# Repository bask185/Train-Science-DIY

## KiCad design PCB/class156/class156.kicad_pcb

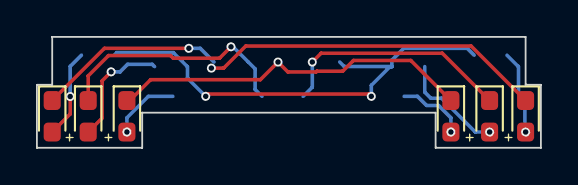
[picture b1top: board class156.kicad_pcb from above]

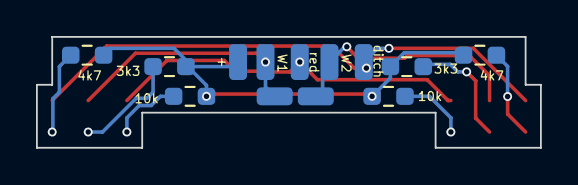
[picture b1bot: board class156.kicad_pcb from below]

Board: 2 copper layers, 28.0 x 6.2 mm, 19 parts (13 on the bottom side), 11 nets.

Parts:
D1, D2, D3, D4, D5, D6: LED; LED_0603_1608Metric_Pad1.05x0.95mm_HandSolder
J1: ditch; SolderWirePad_1x01_SMD_1x2mm
J2, J6: W1; SolderWirePad_1x01_SMD_1x2mm
J3: red; SolderWirePad_1x01_SMD_1x2mm
J4: Conn_01x01_Pin; SolderWirePad_1x01_SMD_1x2mm
J5, J7: W3; SolderWirePad_1x01_SMD_1x2mm
R1, R6: 4k7; R_0603_smalltext
R2, R5: 3k3; R_0603_smalltext
R3, R4: 10k; R_0603_smalltext

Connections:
unnamed: D1.2 (A), R1.2
unnamed: D1.1 (K), D6.1 (K), J1.1
unnamed: D2.2 (A), R2.2
unnamed: D2.1 (K), J2.1, J6.1
unnamed: D3.2 (A), R3.2
unnamed: D3.1 (K), D4.1 (K), J3.1
unnamed: D4.2 (A), R4.2
unnamed: D5.2 (A), R5.2
unnamed: D5.1 (K), J5.1, J7.1
unnamed: D6.2 (A), R6.2
VCC: J4.1, R1.1, R2.1, R3.1, R4.1, R5.1, R6.1

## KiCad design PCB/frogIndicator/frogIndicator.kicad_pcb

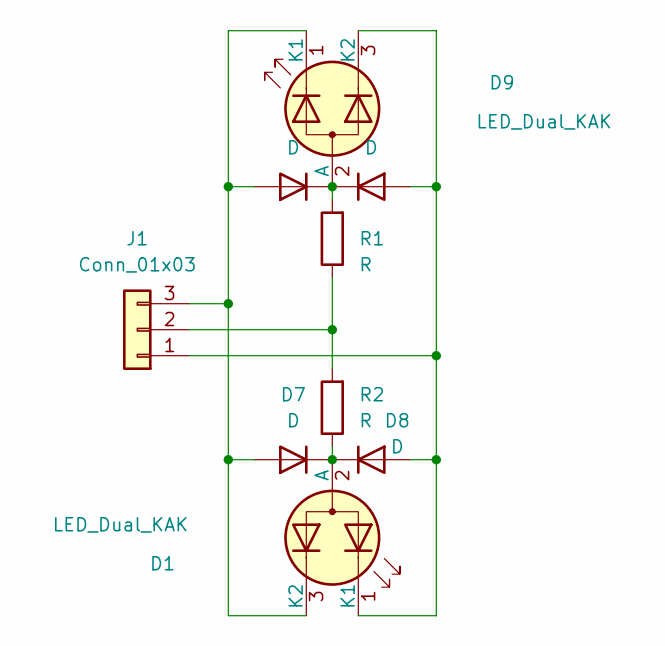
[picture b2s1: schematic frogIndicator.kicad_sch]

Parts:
D1, D9: LED_Dual_KAK; LED_D3.0mm-3
D5, D6, D7, D8: D; D_DO-34_SOD68_P7.62mm_Horizontal
J1: Conn_01x03; TerminalBlock_Phoenix_MKDS-1,5-3-5.08_1x03_P5.08mm_Horizont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
R1, R2: R; R_Axial_DIN0204_L3.6mm_D1.6mm_P7.62mm_Horizontal

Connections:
unnamed: D1.2 (A), D7.1 (K), D8.1 (K), R2.1
unnamed: D1.1 (K1), D6.2 (A), D8.2 (A), D9.3 (K2), J1.1
unnamed: D1.3 (K2), D5.2 (A), D7.2 (A), D9.1 (K1), J1.3
unnamed: D5.1 (K), D6.1 (K), D9.2 (A), R1.2
unnamed: J1.2, R1.1, R2.2

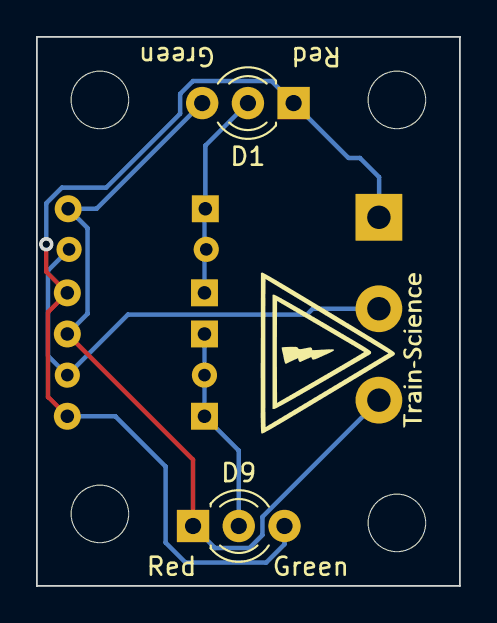
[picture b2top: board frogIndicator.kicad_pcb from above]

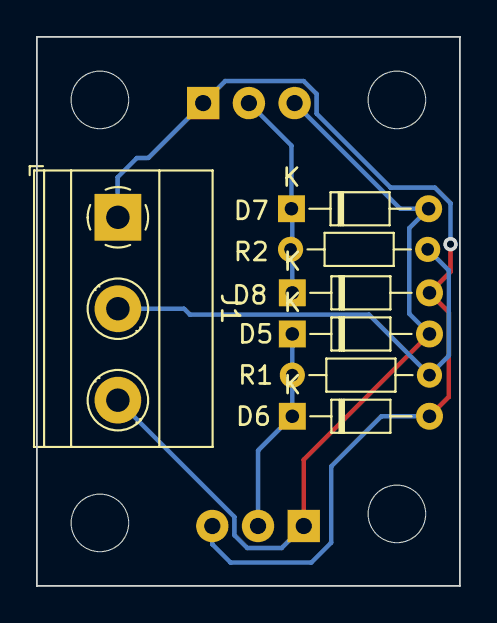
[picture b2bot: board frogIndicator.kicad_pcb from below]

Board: 2 copper layers, 23.5 x 30.5 mm, 9 parts (7 on the bottom side), 5 nets.

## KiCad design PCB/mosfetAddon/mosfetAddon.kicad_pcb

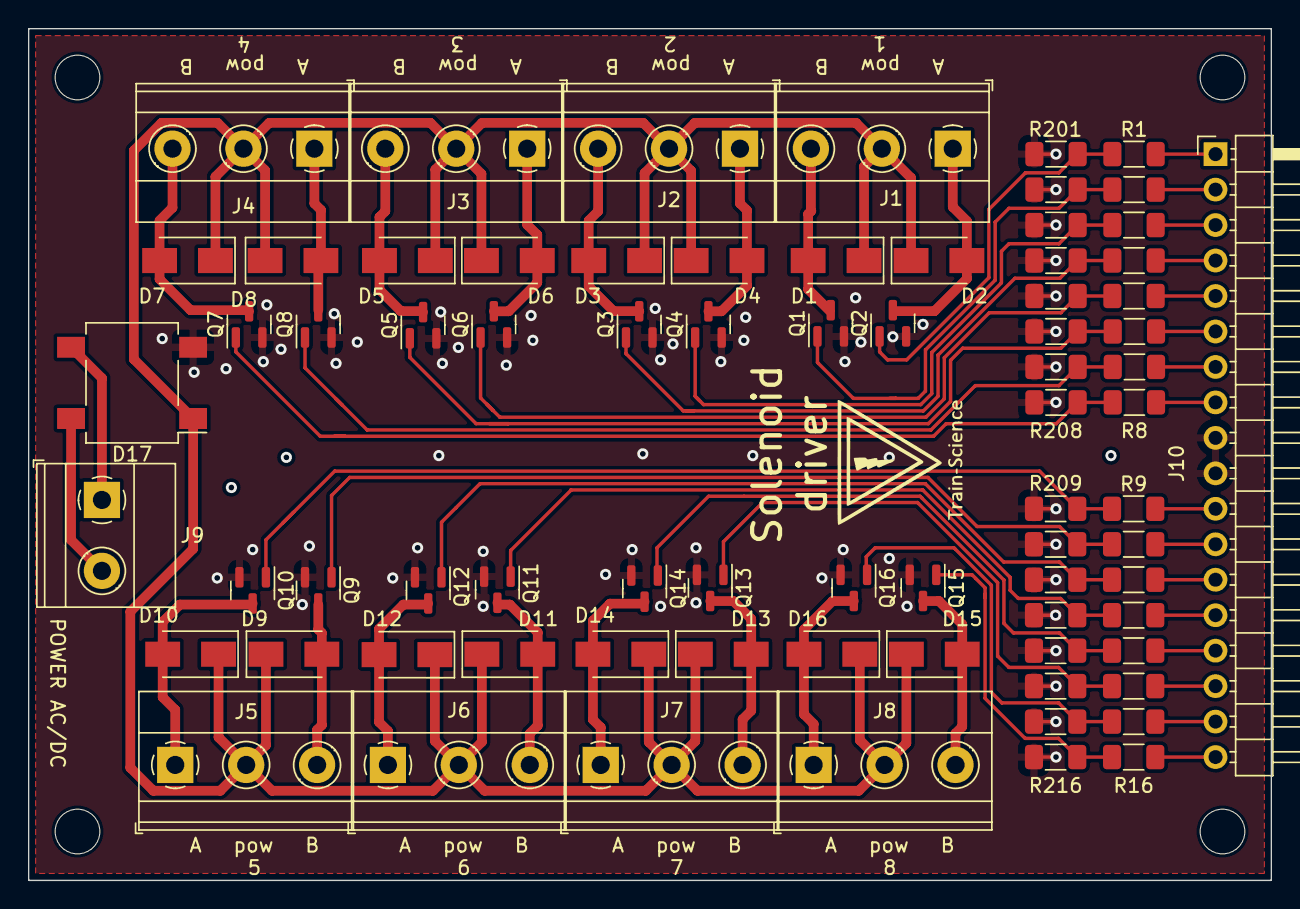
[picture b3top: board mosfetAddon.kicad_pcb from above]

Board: 2 copper layers, 89.0 x 61.0 mm, 75 parts (0 on the bottom side), 52 nets.

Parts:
D1, D2, D3, D4, D5, D6, D7, D8, D9, D10, D11, D12, D13, D14, D15, D16: D; D_SMA
D17: D_Bridge_+-AA; Diode_Bridge_Diotec_SO-DIL-Slim
J1, J2, J3, J4, J5, J6, J7, J8: coil; TerminalBlock_Phoenix_MKDS-1,5-3-5.08_1x03_P5.08mm_Horizont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
J9: pow; TerminalBlock_Phoenix_MKDS-1,5-2-5.08_1x02_P5.08mm_Horizont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
J10: Conn_01x18_Male; PinHeader_1x18_P2.54mm_Horizontal
Q1, Q2, Q3, Q4, Q5, Q6, Q7, Q8, Q9, Q10, Q11, Q12, Q13, Q14, Q15, Q16: AO3400A; SOT-23
R1, R2, R3, R4, R5, R6, R7, R8, R9, R10, R11, R12, R13, R14, R15, R16: 22R; R_1206_3216Metric_Pad1.30x1.75mm_HandSolder
R201, R202, R203, R204, R205, R206, R207, R208, R209, R210, R211, R212, R213, R214, R215, R216: 10k; R_1206_3216Metric_Pad1.30x1.75mm_HandSolder

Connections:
GND: D17.2 (-), J10.9, J10.10, Q1.2 (S), Q2.2 (S), Q3.2 (S), Q4.2 (S), Q5.2 (S), Q6.2 (S), Q7.2 (S), Q8.2 (S), Q9.2 (S), Q10.2 (S), Q11.2 (S), Q12.2 (S), Q13.2 (S), Q14.2 (S), Q15.2 (S), Q16.2 (S), R201.1, R202.1, R203.1, R204.1, R205.1, R206.1, R207.1, R208.1, R209.1, R210.1, R211.1, R212.1, R213.1, R214.1, R215.1, R216.1
unnamed: D17.3, J9.1
unnamed: D17.4, J9.2
unnamed: Q2.1 (G), R1.2, R201.2
unnamed: Q1.1 (G), R2.2, R202.2
unnamed: Q4.1 (G), R3.2, R203.2
unnamed: Q3.1 (G), R4.2, R204.2
unnamed: Q6.1 (G), R5.2, R205.2
unnamed: Q5.1 (G), R6.2, R206.2
unnamed: Q8.1 (G), R7.2, R207.2
unnamed: Q7.1 (G), R8.2, R208.2
unnamed: Q10.1 (G), R9.2, R209.2
unnamed: Q9.1 (G), R10.2, R210.2
unnamed: Q12.1 (G), R11.2, R211.2
unnamed: Q11.1 (G), R12.2, R212.2
unnamed: Q14.1 (G), R13.2, R213.2
unnamed: Q13.1 (G), R14.2, R214.2
unnamed: Q16.1 (G), R15.2, R215.2
unnamed: Q15.1 (G), R16.2, R216.2
coil1L: D1.2 (A), J1.3, Q1.3 (D)
coil1R: D2.2 (A), J1.1, Q2.3 (D)
coil2L: D3.2 (A), J2.3, Q3.3 (D)
coil2R: D4.2 (A), J2.1, Q4.3 (D)
coil3L: D5.2 (A), J3.3, Q5.3 (D)
coil3R: D6.2 (A), J3.1, Q6.3 (D)
coil4L: D7.2 (A), J4.3, Q7.3 (D)
coil4R: D8.2 (A), J4.1, Q8.3 (D)
coil5L: D9.2 (A), J5.3, Q9.3 (D)
coil5R: D10.2 (A), J5.1, Q10.3 (D)
coil6L: D11.2 (A), J6.3, Q11.3 (D)
coil6R: D12.2 (A), J6.1, Q12.3 (D)
coil7L: D13.2 (A), J7.3, Q13.3 (D)
coil7R: D14.2 (A), J7.1, Q14.3 (D)
coil8L: D15.2 (A), J8.3, Q15.3 (D)
coil8R: D16.2 (A), J8.1, Q16.3 (D)
gate1L: J10.2, R2.1
gate1R: J10.1, R1.1
gate2L: J10.4, R4.1
gate2R: J10.3, R3.1
gate3L: J10.6, R6.1
gate3R: J10.5, R5.1
gate4L: J10.8, R8.1
gate4R: J10.7, R7.1
gate5L: J10.12, R10.1
gate5R: J10.11, R9.1
gate6L: J10.14, R12.1
gate6R: J10.13, R11.1
gate7L: J10.16, R14.1
gate7R: J10.15, R13.1
gate8L: J10.18, R16.1
gate8R: J10.17, R15.1
pow: D1.1 (K), D2.1 (K), D3.1 (K), D4.1 (K), D5.1 (K), D6.1 (K), D7.1 (K), D8.1 (K), D9.1 (K), D10.1 (K), D11.1 (K), D12.1 (K), D13.1 (K), D14.1 (K), D15.1 (K), D16.1 (K), D17.1 (+), J1.2, J2.2, J3.2, J4.2, J5.2, J6.2, J7.2, J8.2

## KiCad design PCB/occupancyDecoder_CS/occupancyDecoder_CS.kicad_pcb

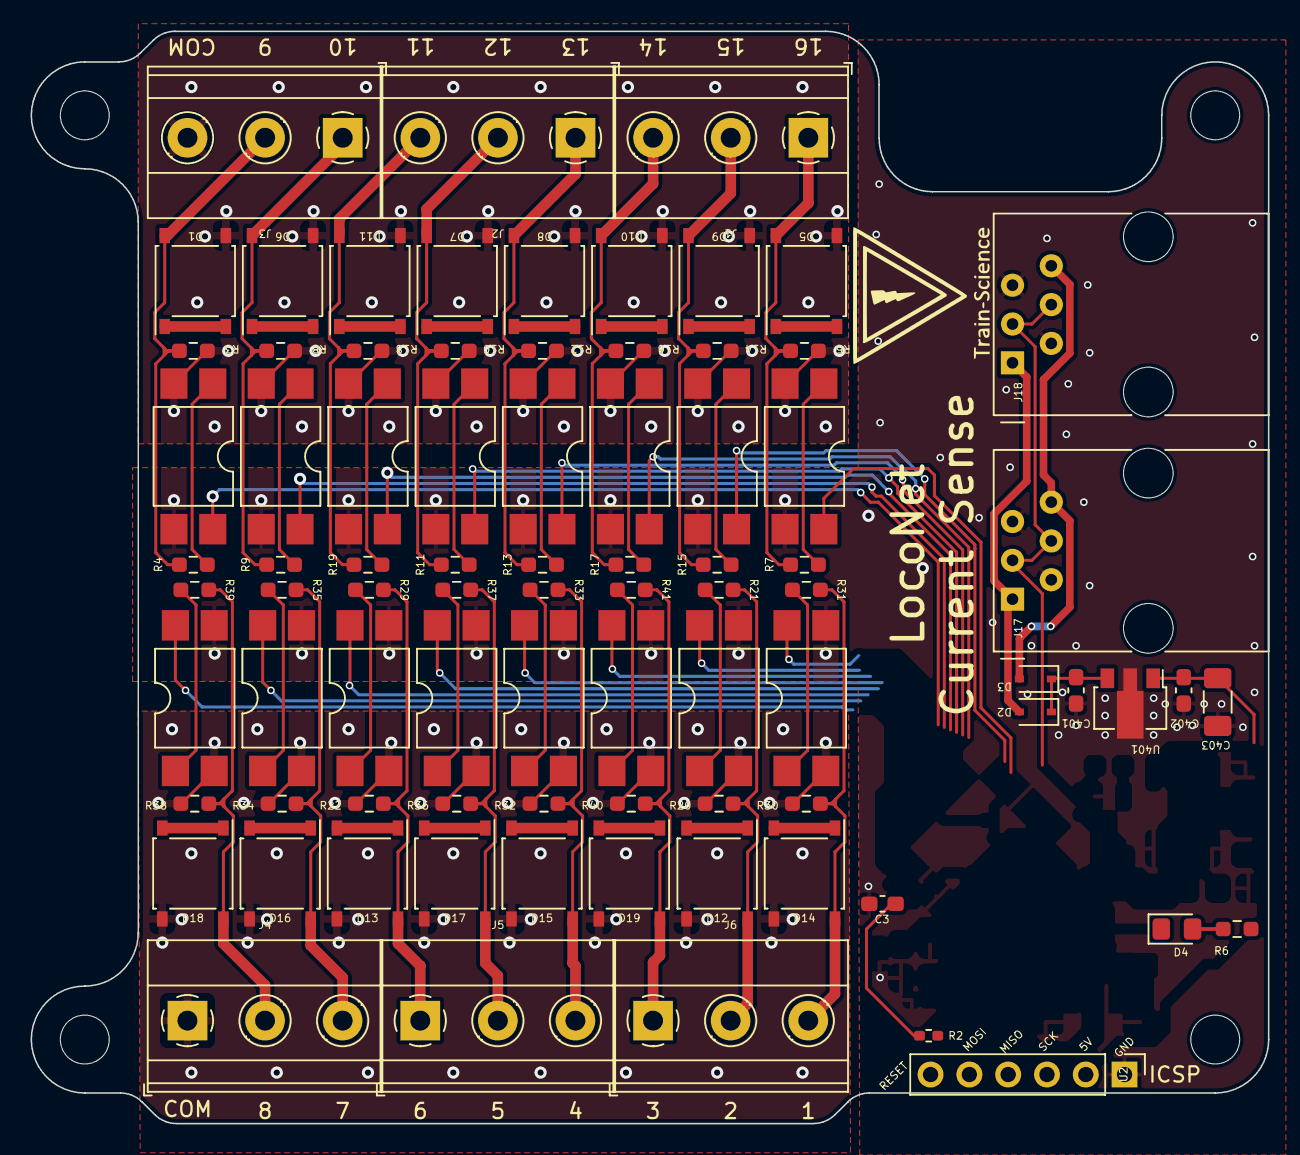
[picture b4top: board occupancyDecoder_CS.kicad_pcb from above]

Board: 2 copper layers, 81.0 x 71.5 mm, 83 parts (0 on the bottom side), 61 nets.

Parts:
C3, C402: 100nF; C_0603_1608Metric_Pad1.08x0.95mm_HandSolder
C401: 330nF; C_0603_1608Metric_Pad1.08x0.95mm_HandSolder
C403: 100uF; C_1206_3216Metric_Pad1.33x1.80mm_HandSolder
D1, D5, D6, D7, D8, D9, D10, D11, D12, D13, D14, D15, D16, D17, D18, D19: ABS2; Diode_Bridge_Diotec_ABS
D2, D3: D; D_SOD-323
D4: LED; LED_0805_2012Metric_Pad1.15x1.40mm_HandSolder
J1, J2, J3, J4, J5, J6: Screw_Terminal_01x03; TerminalBlock_Phoenix_MKDS-1,5-3-5.08_1x03_P5.08mm_Horizont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
J17, J18: RJ12; RJ12_Amphenol_54601
R2: 10k; R_0402_1005Metric_Pad0.72x0.64mm_HandSolder
R3, R5, R8, R10, R12, R14, R16, R18, R20, R22, R30, R32, R34, R36, R38, R40: 4k7; R_0603_smalltext
R4, R7, R9, R11, R13, R15, R17, R19, R21, R29, R31, R33, R35, R37, R39, R41: 47R; R_0603_smalltext
R6: 6k2; R_0603_1608Metric_Pad0.98x0.95mm_HandSolder
U2: ICSP; PinHeader_1x06_P2.54mm_Vertical
U3, U4, U5, U6, U7, U8, U9, U10, U11, U12, U13, U14, U16, U17, U18, U19: EL814; SMDIP-4_W9.53mm
U401: L78L05_SOT89; SOT-89-3

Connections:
+5V: C3.2, C402.1, C403.1, R2.1, R6.1, U2.2, U401.1 (OUT)
/GPIO_A/CS1/COM: D12.3, D13.3, D14.3, D15.3, D16.3, D17.3, D18.3, D19.3, J4.1, R20.2, R22.2, R30.2, R32.2, R34.2, R36.2, R38.2, R40.2, U11.2, U12.2, U13.2, U14.2, U16.2, U17.2, U18.2, U19.2
/GPIO_A/CS1/Track: D14.4, J6.3, R30.1, R31.1
/GPIO_A/CS2/Track: D12.4, J6.2, R20.1, R21.1
/GPIO_A/CS3/Track: D19.4, J6.1, R40.1, R41.1
/GPIO_A/CS4/Track: D15.4, J5.3, R32.1, R33.1
/GPIO_A/CS5/Track: D17.4, J5.2, R36.1, R37.1
/GPIO_A/CS6/Track: D13.4, J5.1, R22.1, R29.1
/GPIO_A/CS7/Track: D16.4, J4.3, R34.1, R35.1
/GPIO_A/CS8/Track: D18.4, J4.2, R38.1, R39.1
/GPIO_A/GPIO_A5: U2.5, U17.4
/GPIO_A/GPIO_A6: U2.4, U12.4
/GPIO_B/CS1/COM: D1.3, D5.3, D6.3, D7.3, D8.3, D9.3, D10.3, D11.3, J3.3, R3.2, R5.2, R8.2, R10.2, R12.2, R14.2, R16.2, R18.2, U3.2, U4.2, U5.2, U6.2, U7.2, U8.2, U9.2, U10.2
/GPIO_B/CS1/Track: D1.4, J3.2, R3.1, R4.1
/GPIO_B/CS2/Track: D6.4, J3.1, R8.1, R9.1
/GPIO_B/CS3/Track: D11.4, J2.3, R18.1, R19.1
/GPIO_B/CS4/Track: D7.4, J2.2, R10.1, R11.1
/GPIO_B/CS5/Track: D8.4, J2.1, R12.1, R13.1
/GPIO_B/CS6/Track: D10.4, J1.3, R16.1, R17.1
/GPIO_B/CS7/Track: D9.4, J1.2, R14.1, R15.1
/GPIO_B/CS8/Track: D5.4, J1.1, R5.1, R7.1
/Lnet/Loconet: J18.3, J18.4
GND: C3.1, C401.2, C402.2, C403.2, J17.2, J17.5, J18.2, J18.5, U2.1, U3.3, U4.3, U5.3, U6.3, U7.3, U8.3, U9.3, U10.3, U11.3, U12.3, U13.3, U14.3, U16.3, U17.3, U18.3, U19.3, U401.2 (GND)
LED: D4.1 (K), U2.3
unnamed: D1.1 (+), D1.2 (-)
unnamed: D2.2 (A), J17.1, J18.1
unnamed: D3.2 (A), J17.6, J18.6
unnamed: D4.2 (A), R6.2
unnamed: D5.1 (+), D5.2 (-)
unnamed: D6.1 (+), D6.2 (-)
unnamed: D7.1 (+), D7.2 (-)
unnamed: D8.1 (+), D8.2 (-)
unnamed: D9.1 (+), D9.2 (-)
unnamed: D10.1 (+), D10.2 (-)
unnamed: D11.1 (+), D11.2 (-)
unnamed: D12.1 (+), D12.2 (-)
unnamed: D13.1 (+), D13.2 (-)
unnamed: D14.1 (+), D14.2 (-)
unnamed: D15.1 (+), D15.2 (-)
unnamed: D16.1 (+), D16.2 (-)
unnamed: D17.1 (+), D17.2 (-)
unnamed: D18.1 (+), D18.2 (-)
unnamed: D19.1 (+), D19.2 (-)
unnamed: R4.2, U3.1
unnamed: R7.2, U4.1
unnamed: R9.2, U5.1
unnamed: R11.2, U6.1
unnamed: R13.2, U7.1
unnamed: R15.2, U8.1
unnamed: R17.2, U9.1
unnamed: R19.2, U10.1
unnamed: R21.2, U11.1
unnamed: R29.2, U12.1
unnamed: R31.2, U13.1
unnamed: R33.2, U14.1
unnamed: R35.2, U16.1
unnamed: R37.2, U17.1
unnamed: R39.2, U18.1
unnamed: R41.2, U19.1
RESET: R2.2, U2.6
VCC: C401.1, D2.1 (K), D3.1 (K), U401.3 (IN)

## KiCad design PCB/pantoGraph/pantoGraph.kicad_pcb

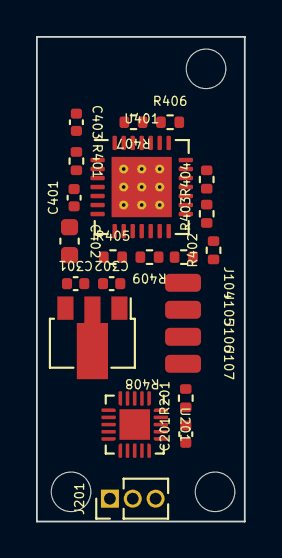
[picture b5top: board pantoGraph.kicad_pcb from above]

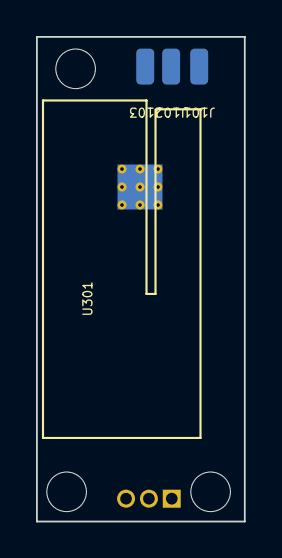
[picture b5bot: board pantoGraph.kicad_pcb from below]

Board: 2 copper layers, 11.5 x 26.9 mm, 27 parts (3 on the bottom side), 20 nets, no tracks yet.

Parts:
C201, C302, C401, C403: 100nF; C_0402_1005Metric
C301: 330nF; C_0402_1005Metric
C402: 220nF; C_0603_1608Metric
J101, J102, J103, J104, J105, J106, J107: Conn_01x01_Pin; SolderWirePad_1x01_SMD_1x2mm
J201: Conn_01x03_Pin; PinHeader_1x03_P1.27mm_Vertical
R201: R; R_0402_1005Metric
R401, R402, R405: 100k; R_0402_1005Metric
R403, R404, R408: R_Small; R_0402_1005Metric
R406, R407: 1R; R_0402_1005Metric
R409: 10k; R_0402_1005Metric
U201: ATtiny1616-M; VQFN-20-1EP_3x3mm_P0.4mm_EP1.7x1.7mm
U301: L78L05_SOT89; SOT-89-3
U401: QFN-28-1EP_5x5mm_P0.5mm_EP3.35x3.35mm_ThermalVias

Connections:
+5V: C201.2, C302.1, J201.2, R201.1, U201.4 (VCC), U301.1 (OUT)
/SIG: J101.1, U201.7 (PA6)
/a4988/5V: R402.1, R403.1, R405.1, R408.1, U401.15 (VDD)
/a4988/DIR: U201.2 (PA3), U401.19 (DIR)
/a4988/STEP: U201.5 (PA4), U401.16 (STEP)
/a4988/VCC: C403.1, U401.22 (VBB1), U401.28 (VBB2)
/a4988/~ENABLE: R401.1, U201.1 (PA2), U401.2 (~Enable)
/attiny/UPDI: J201.1, R201.2, U201.19 (~RESET/PA0)
GND: C201.1, C301.2, C302.2, C402.2, J103.1, J201.3, R401.2, R404.2, R406.2, R407.2, R409.2, U201.3 (GND), U201.21 (GND), U301.2 (GND), U401.3 (GND), U401.9 (MS1), U401.10 (MS2), U401.11 (MS3), U401.18 (GND), U401.29 (GND)
unnamed: C401.2, U401.4 (CP1)
unnamed: C401.1, U401.5 (CP2)
unnamed: R403.2, R404.1, U401.17 (REF)
unnamed: R408.2, R409.1, U401.13 (ROSC)
unnamed: R406.1, U401.23 (SENSE1)
unnamed: R407.1, U401.27 (SENSE2)
unnamed: C403.2, U401.6 (VCP)
unnamed: C402.1, U401.8 (Vreg)
unnamed: R405.2, U401.12 (~RESET)
unnamed: R402.2, U401.14 (~SLEEP)
VCC: C301.1, J102.1, U301.3 (IN)

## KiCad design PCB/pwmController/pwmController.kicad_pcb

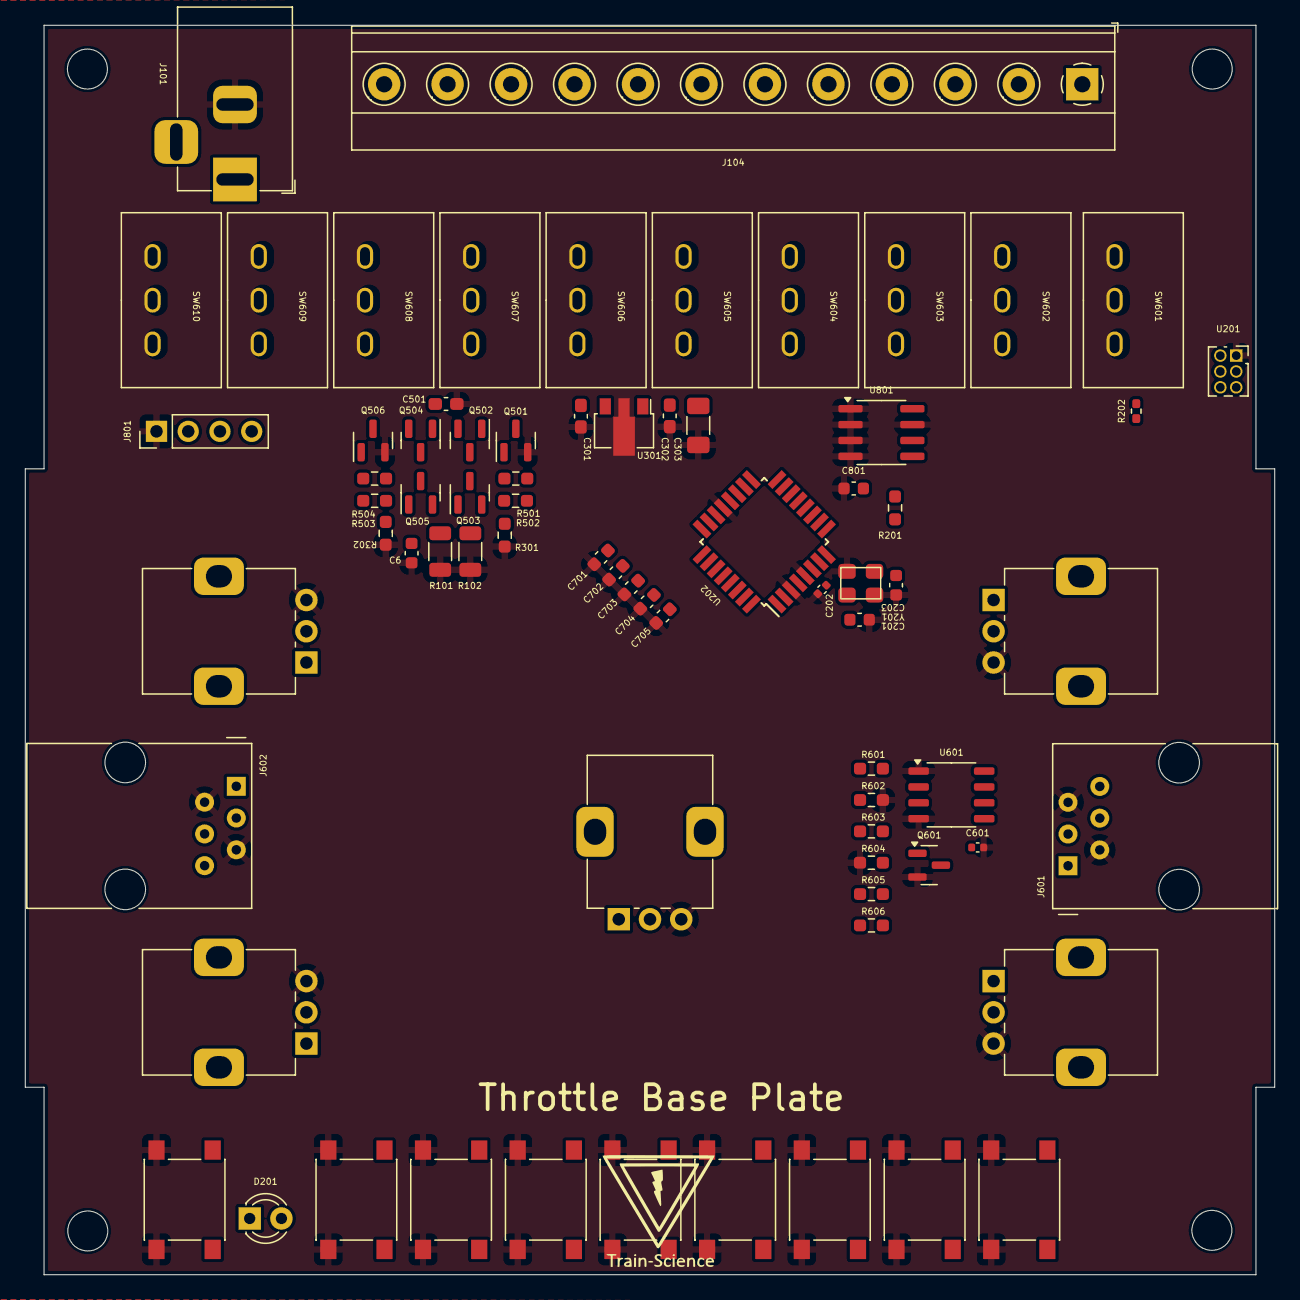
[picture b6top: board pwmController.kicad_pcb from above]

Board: 2 copper layers, 100.0 x 100.0 mm, 74 parts (0 on the bottom side), 51 nets, no tracks yet.

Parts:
C6, C701, C702, C703, C704, C705, C801: 100nF; C_0603_1608Metric
C201, C203: 12pF; C_0603_1608Metric
C202, C601: 100nF; C_0402_1005Metric
C301: 330nF; C_0603_1608Metric_Pad1.08x0.95mm_HandSolder
C302, C501: 100nF; C_0603_1608Metric_Pad1.08x0.95mm_HandSolder
C303: 100uF; C_1206_3216Metric_Pad1.33x1.80mm_HandSolder
D201: LED; LED_D3.0mm
J101: Jack-DC; BarrelJack_Horizontal
J104: Screw_Terminal_01x12; TerminalBlock_Phoenix_MKDS-1,5-12-5.08_1x12_P5.08mm_Horizon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
J601, J602: RJ12
J801: Conn_01x04; PinHeader_1x04_P2.54mm_Vertical
Q501, Q506, Q601: NPN_TOR; SOT-23
Q502, Q504: P-channel; SOT-23
Q503, Q505: N-channel; SOT-23
R101, R102: 0R1; R_1206_3216Metric
R201: 6k2; R_0603_1608Metric_Pad0.98x0.95mm_HandSolder
R202: 10k; R_0402_1005Metric_Pad0.72x0.64mm_HandSolder
R301, R302: 15k; R_0603_smalltext
R501, R504, R605: 1k; R_0603_smalltext
R502, R503, R603: 10k; R_0603_smalltext
R601: 47k; R_0603_smalltext
R602: 150k; R_0603_smalltext
R604: 22k; R_0603_smalltext
R606: 220k; R_0603_smalltext
RV701, RV702, RV703, RV704, RV705: R_Potentiometer; Potentiometer_Alps_RK09K_Single_Vertical
SW101, SW1001, SW1002, SW1003, SW1004, SW1005, SW1006, SW1007, SW1008: SW_Push; tactile_SMD_6mm
SW601, SW602, SW603, SW604, SW605, SW606, SW607, SW608, SW609, SW610: SW_SPDT; MTS_long_lever
U201: HEADER_3x2; PinSocket_2x03_P1.27mm_Vertical
U202: ATmega328-A; TQFP-32_7x7mm_P0.8mm
U301: L78L05_SOT89; SOT-89-3
U601: LM311; SOP-8_3.9x4.9mm_P1.27mm
U801: 24LC256; SOIC-8_3.9x4.9mm_P1.27mm
Y201: Crystal_GND2; crystal_arduino

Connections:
+5V: C202.1, C302.1, C303.1, C601.1, C801.2, J801.2, R201.1, R202.1, R603.1, RV701.1, RV702.1, RV703.1, RV704.1, RV705.1, U201.5, U202.4 (VCC), U202.6 (VCC), U202.18 (AVCC), U301.1 (OUT), U601.8 (V+), U801.8 (VCC)
+12V: C301.1, C501.2, J101.1, Q502.2 (S), Q504.2 (S), R502.1, R503.1, U301.3 (IN)
/EEPROM/SCL: J801.4, U202.28 (PC5), U801.6 (SCL)
/EEPROM/SDA: J801.3, U202.27 (PC4), U801.5 (SDA)
/H-bridge/CurrentSense: C6.1, Q503.2 (S), Q505.2 (S), R101.1, R102.1, U202.22 (ADC7)
/H-bridge/IN_A: R501.1, U202.10 (PD6)
/H-bridge/IN_B: R504.2, U202.11 (PD7)
/Lnet/Rx: R606.2, U202.12 (PB0), U601.7
/Lnet/Tx: R605.2, U202.13 (PB1)
/Potentiometers/POT1: C701.2, RV701.2, U202.23 (PC0)
/Potentiometers/POT2: C702.1, RV702.2, U202.24 (PC1)
/Potentiometers/POT3: C703.1, RV703.2, U202.25 (PC2)
/Potentiometers/POT4: C704.1, RV704.2, U202.26 (PC3)
/Potentiometers/POT5: C705.1, RV705.2, U202.19 (ADC6)
/atmega/LED: D201.1 (K), U201.4, U202.17 (PB5)
/atmega/MISO: SW101.2, U201.6, U202.16 (PB4)
/atmega/X1: C201.2, U202.7 (XTAL1/PB6), Y201.1
/atmega/X2: C203.2, U202.8 (XTAL2/PB7), Y201.3
/atmega/reset: R202.2, U201.2, U202.29 (~RESET/PC6)
/atmega/slot1: SW1001.2, U202.30 (PD0)
/atmega/slot2: SW1002.2, U202.31 (PD1)
/atmega/slot3: SW1003.2, U202.32 (PD2)
/atmega/slot4: SW1004.2, U202.1 (PD3)
/atmega/slot5: SW1005.2, U202.2 (PD4)
/atmega/slot6: SW1006.2, U202.9 (PD5)
/atmega/slot7: SW1007.2, U202.14 (PB2)
/atmega/slot8: SW1008.2, U201.3, U202.15 (PB3)
/trackFront: J104.11, Q502.3 (D), Q503.3 (D), SW601.2 (B), SW602.2 (B), SW603.2 (B), SW604.2 (B), SW605.2 (B), SW606.2 (B), SW607.2 (B), SW608.2 (B), SW609.2 (B), SW610.2 (B)
/trackRear: J104.12, Q504.3 (D), Q505.3 (D)
GND: C6.2, C201.1, C202.2, C203.1, C301.2, C302.2, C303.2, C501.1, C601.2, C701.1, C702.2, C703.2, C704.2, C705.2, C801.1, J101.2, J601.2, J601.5, J602.2, J602.5, J801.1, Q501.2 (E), Q506.2 (E), Q601.2 (E), R101.2, R102.2, R301.1, R302.2, R602.2, R604.1, RV701.3, RV702.3, RV703.3, RV704.3, RV705.3, SW101.1, SW1001.1, SW1002.1, SW1003.1, SW1004.1, SW1005.1, SW1006.1, SW1007.1, SW1008.1, U201.1, U202.3 (GND), U202.5 (GND), U202.21 (GND), U301.2 (GND), U601.1 (GND), U601.4 (V-), U801.1 (A0), U801.2 (A1), U801.3 (A2), U801.4 (GND), U801.7 (WP), Y201.2 (GND), Y201.4 (GND)
unnamed: D201.2 (A), R201.2
unnamed: J104.1, SW601.1 (A)
unnamed: J104.2, SW602.1 (A)
unnamed: J104.3, SW603.1 (A)
unnamed: J104.4, SW604.1 (A)
unnamed: J104.5, SW605.1 (A)
unnamed: J104.6, SW606.1 (A)
unnamed: J104.7, SW607.1 (A)
unnamed: J104.8, SW608.1 (A)
unnamed: J104.9, SW609.1 (A)
unnamed: J104.10, SW610.1 (A)
unnamed: J601.1, J602.1
unnamed: J601.6, J602.6
unnamed: Q501.1 (B), R501.2
unnamed: Q501.3 (C), Q502.1 (G), Q503.1 (G), R301.2, R502.2
unnamed: Q504.1 (G), Q505.1 (G), Q506.3 (C), R302.1, R503.2
unnamed: Q506.1 (B), R504.1
unnamed: Q601.1 (B), R605.1
unnamed: J601.3, J601.4, J602.3, J602.4, Q601.3 (C), R601.1
unnamed: R601.2, R602.1, R606.1, U601.2 (+)
unnamed: R603.2, R604.2, U601.3 (-)

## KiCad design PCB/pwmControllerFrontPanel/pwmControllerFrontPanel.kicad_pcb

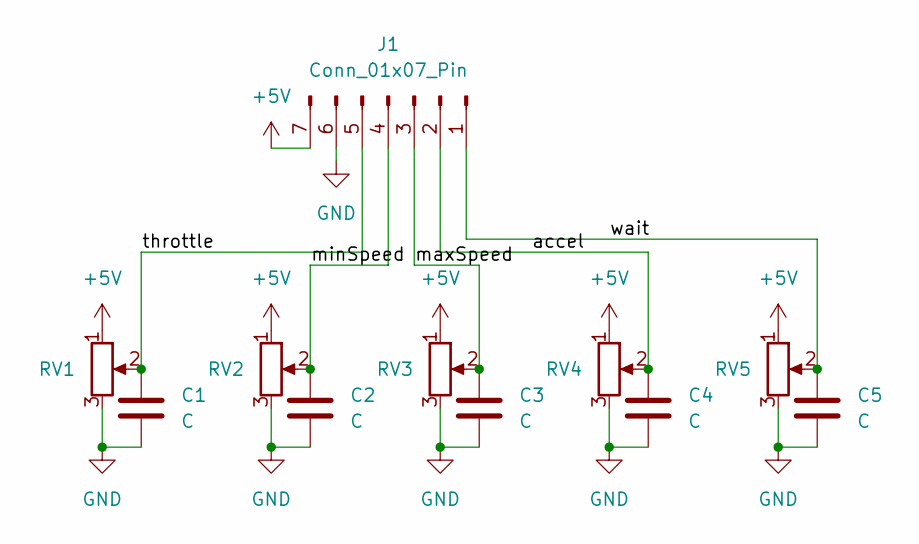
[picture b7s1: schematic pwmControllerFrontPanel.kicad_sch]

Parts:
C1, C2, C3, C4, C5: C; C_Disc_D3.0mm_W1.6mm_P2.50mm
J1: Conn_01x07_Pin; PinHeader_1x07_P2.54mm_Vertical
RV1, RV2, RV3, RV4, RV5: R_Potentiometer; Potentiometer_Alps_RK09K_Single_Vertical

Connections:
+5V: J1.7, RV1.1, RV2.1, RV3.1, RV4.1, RV5.1
/accel: C4.1, J1.2, RV4.2
/maxSpeed: C3.1, J1.3, RV3.2
/minSpeed: C2.1, J1.4, RV2.2
/throttle: C1.1, J1.5, RV1.2
/wait: C5.1, J1.1, RV5.2
GND: C1.2, C2.2, C3.2, C4.2, C5.2, J1.6, RV1.3, RV2.3, RV3.3, RV4.3, RV5.3

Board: 2 copper layers, 11 parts (6 on the bottom side), 7 nets, no tracks yet.
